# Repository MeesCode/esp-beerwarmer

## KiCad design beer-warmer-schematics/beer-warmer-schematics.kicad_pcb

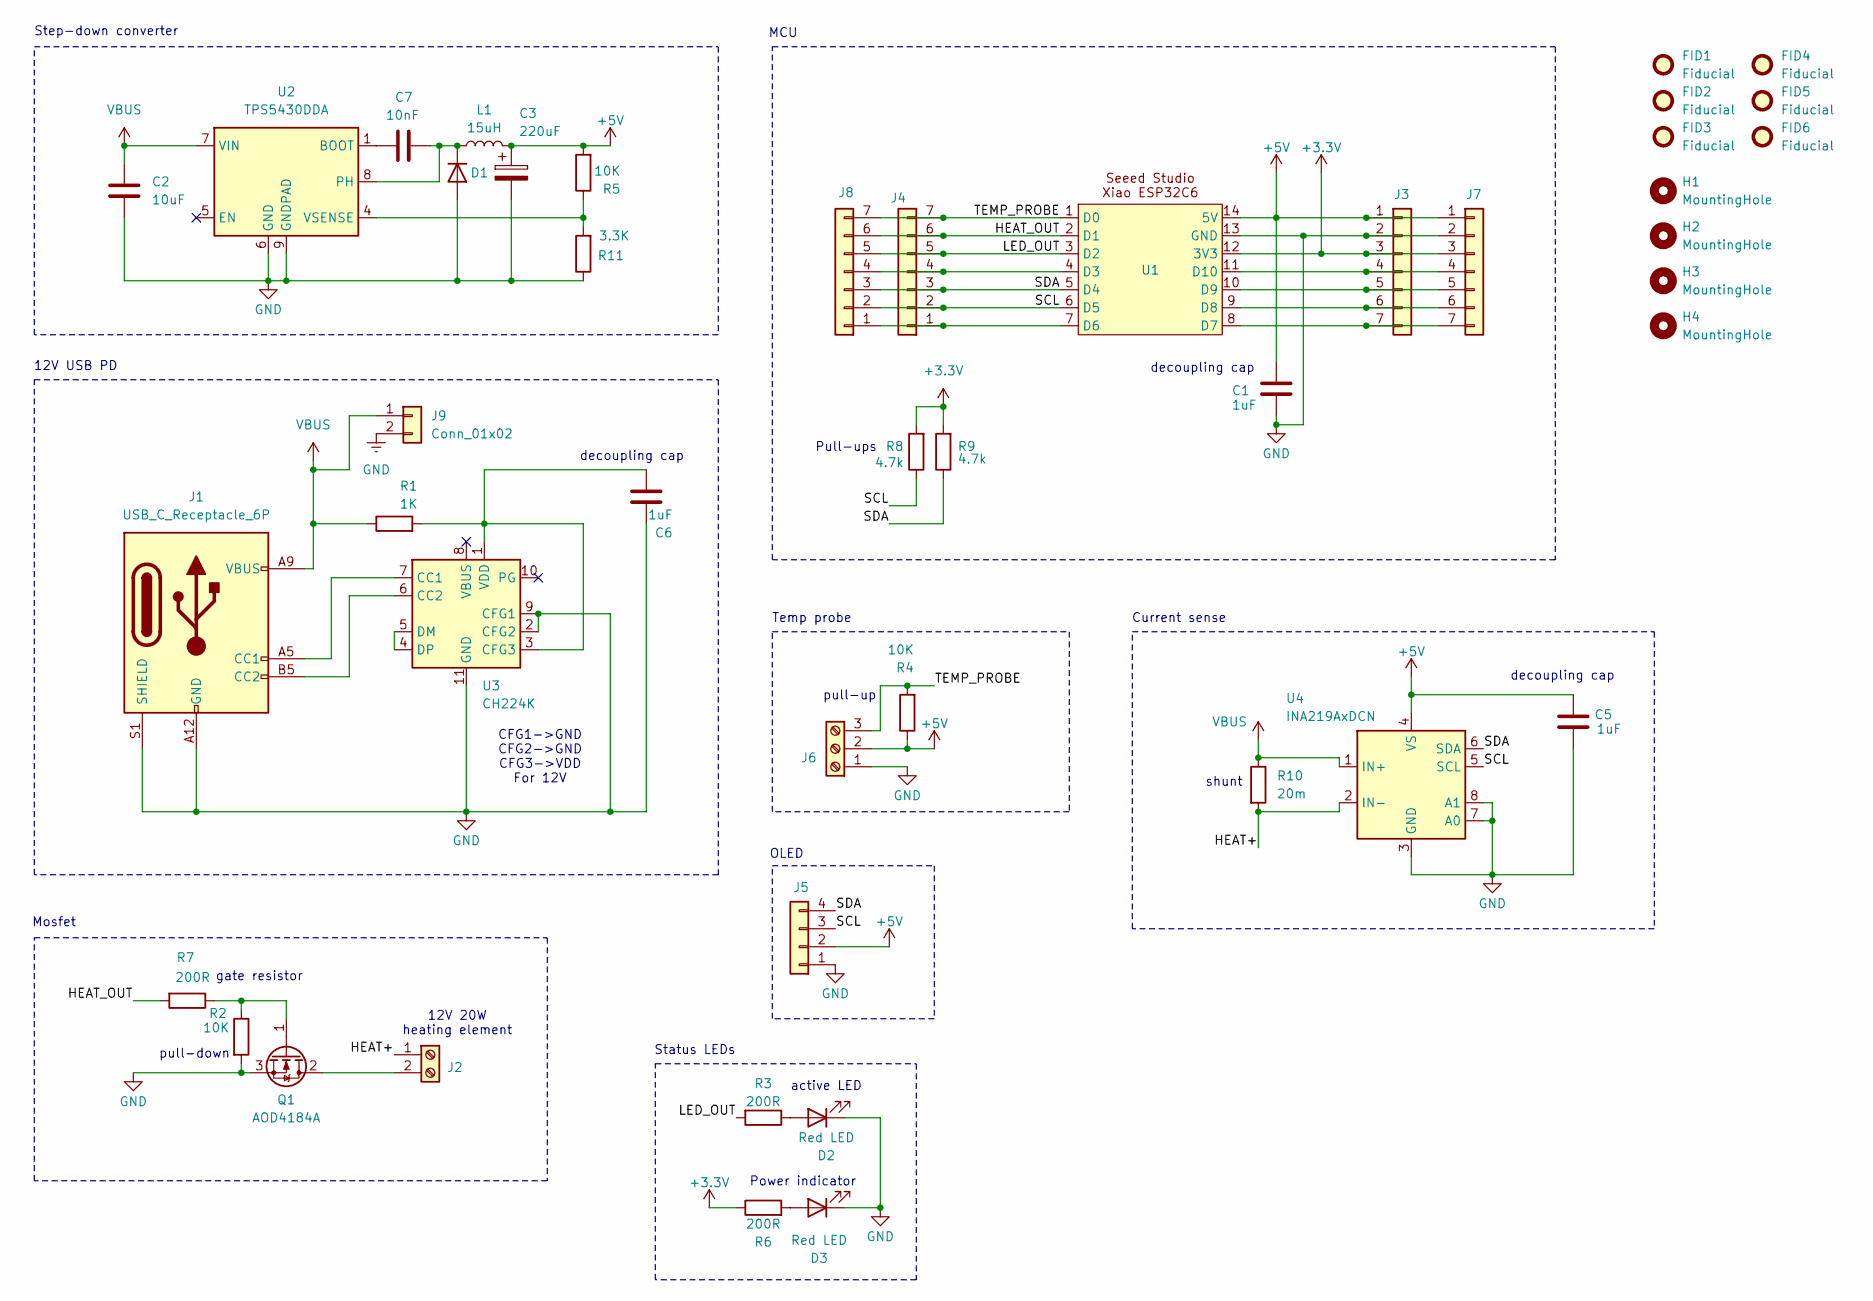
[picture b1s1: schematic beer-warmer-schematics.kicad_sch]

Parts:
C1, C5, C6: 1uF; C_0402_1005Metric; LCSC C52923
C2: 10uF; C_0805_2012Metric; LCSC C15850
C3: 220uF; CP_Elec_6.3x7.7; LCSC C3342
C7: 10nF; C_0402_1005Metric; LCSC C1524
D1: D; D_SMA; Manufacturer # B530C-13-F; LCSC C64982
D2, D3: Red LED; LED_0603_1608Metric; LCSC C2286
FID1, FID2, FID3, FID4, FID5, FID6: Fiducial; Fiducial_0.5mm_Mask1.5mm
H1, H2, H3, H4: MountingHole; MountingHole_3.2mm_M3_DIN965_Pad
J1: USB_C_Receptacle_6P; USB_C_Receptacle_GCT_USB4125-xx-x_6P_TopMnt_Horizontal; Manufacturer # 1054500101; LCSC C456012
J2: Screw_Terminal_01x02; TerminalBlock_Phoenix_MKDS-1,5-2-5.08_1x02_P5.08mm_Horizont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; LCSC C8465
J3, J4: Conn_01x07_Socket; PinSocket_1x07_P2.54mm_Vertical; LCSC C2932672
J5: Conn_01x04_Pin; JST_XH_B4B-XH-A_1x04_P2.50mm_Vertical; LCSC C594232
J6: Screw_Terminal_01x03; TerminalBlock_Phoenix_MKDS-1,5-3-5.08_1x03_P5.08mm_Horizont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; LCSC C72334
J7, J8: Conn_01x07_Socket; PinHeader_1x07_P2.54mm_Vertical; LCSC C2932672
J9: Conn_01x02; PinHeader_1x02_P2.54mm_Vertical
L1: 15uH; L_Changjiang_FNR5040S; LCSC C167969
Q1: AOD4184A; TO-252-2; LCSC C99124
R1: 1K; R_0603_1608Metric; LCSC C21190
R2, R4, R5: 10K; R_0603_1608Metric; LCSC C15401
R3, R6, R7: 200R; R_0603_1608Metric; LCSC C22962
R8, R9: 4.7k; R_0603_1608Metric; LCSC C23162
R10: 20m; R_1206_3216Metric; LCSC C393094
R11: 3.3K; R_0603_1608Metric; LCSC C22978
U1: XIAO-ESP32C6-DIP
U2: TPS5430DDA; TI_SO-PowerPAD-8_ThermalVias; LCSC C9864
U3: CH224K; SSOP-10-1EP_3.9x4.9mm_P1mm_EP2.1x3.3mm; LCSC C970725
U4: INA219AxDCN; SOT-23-8; LCSC C87469

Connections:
+3.3V: J3.3, J7.3, R6.1, R8.2, R9.2, U1.12 (3V3)
+5V: C1.1, C3.1, C5.2, J3.1, J5.2, J6.2, J7.1, L1.2, R4.1, R5.2, U1.14 (5V), U4.4 (VS); also elsewhere on the board
/<NO NET>: J4.4, J8.4, U1.4 (D3)
/HEAT+: J2.1, R10.2, U4.2 (IN-)
/HEAT_OUT: J4.6, J8.6, R7.2, U1.2 (D1)
/LED_OUT: J4.5, J8.5, R3.2, U1.3 (D2)
/SCL: J4.2, J5.3, J8.2, R8.1, U1.6 (D5), U4.5 (SCL)
/SDA: J4.3, J5.4, J8.3, R9.1, U1.5 (D4), U4.6 (SDA)
/TEMP_PROBE: J4.7, J6.3, J8.7, R4.2, U1.1 (D0)
GND: C1.2, C2.2, C3.2, C5.1, C6.1, D1.2 (A), D2.1 (K), D3.1 (K), J1.A12 (GND), J1.B12 (GND), J1.S1 (SHIELD), J3.2, J5.1, J6.1, J7.2, J9.2, Q1.3 (S), R2.2, R11.1, U1.13 (GND), U2.6 (GND), U2.9 (GNDPAD), U3.2 (CFG2), U3.9 (CFG1), U3.11 (GND), U4.3 (GND), U4.7 (A0), U4.8 (A1)
unnamed: C7.1, D1.1 (K), L1.1, U2.8 (PH)
unnamed: D2.2 (A), R3.1
unnamed: D3.2 (A), R6.2
unnamed: J1.A5 (CC1), U3.7 (CC1)
unnamed: J1.B5 (CC2), U3.6 (CC2)
unnamed: J2.2, Q1.2 (D)
unnamed: J3.4, J7.4, U1.11 (D10)
unnamed: J3.5, J7.5, U1.10 (D9)
unnamed: J3.6, J7.6, U1.9 (D8)
unnamed: J3.7, J7.7, U1.8 (D7)
unnamed: J4.1, J8.1, U1.7 (D6)
unnamed: Q1.1 (G), R2.1, R7.1
unnamed: C7.2, U2.1 (BOOT)
unnamed: R5.1, R11.2, U2.4 (VSENSE)
unnamed: C6.2, R1.2, U3.1 (VDD), U3.3 (CFG3)
unnamed: U3.4 (DP), U3.5 (DM)
VBUS: C2.1, J1.A9 (VBUS), J1.B9 (VBUS), J9.1, R1.1, R10.1, U2.7 (VIN), U4.1 (IN+)

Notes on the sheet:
decoupling cap
12V 20W heating element
12V USB PD
Status LEDs
Current sense
OLED
pull-up
Power indicator
gate resistor
shunt
active LED
Step-down converter
Mosfet
Pull-ups
pull-down
CFG1->GND CFG2->GND CFG3->VDD For 12V
MCU
Temp probe

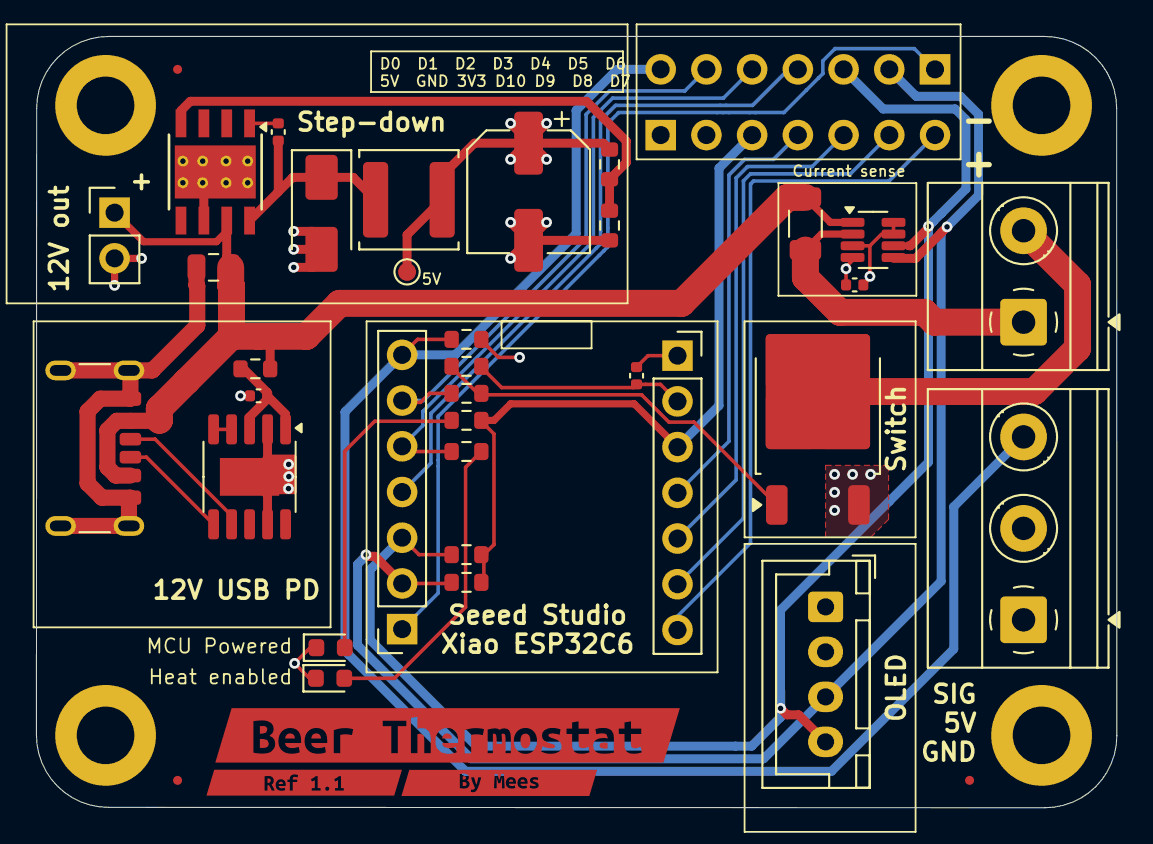
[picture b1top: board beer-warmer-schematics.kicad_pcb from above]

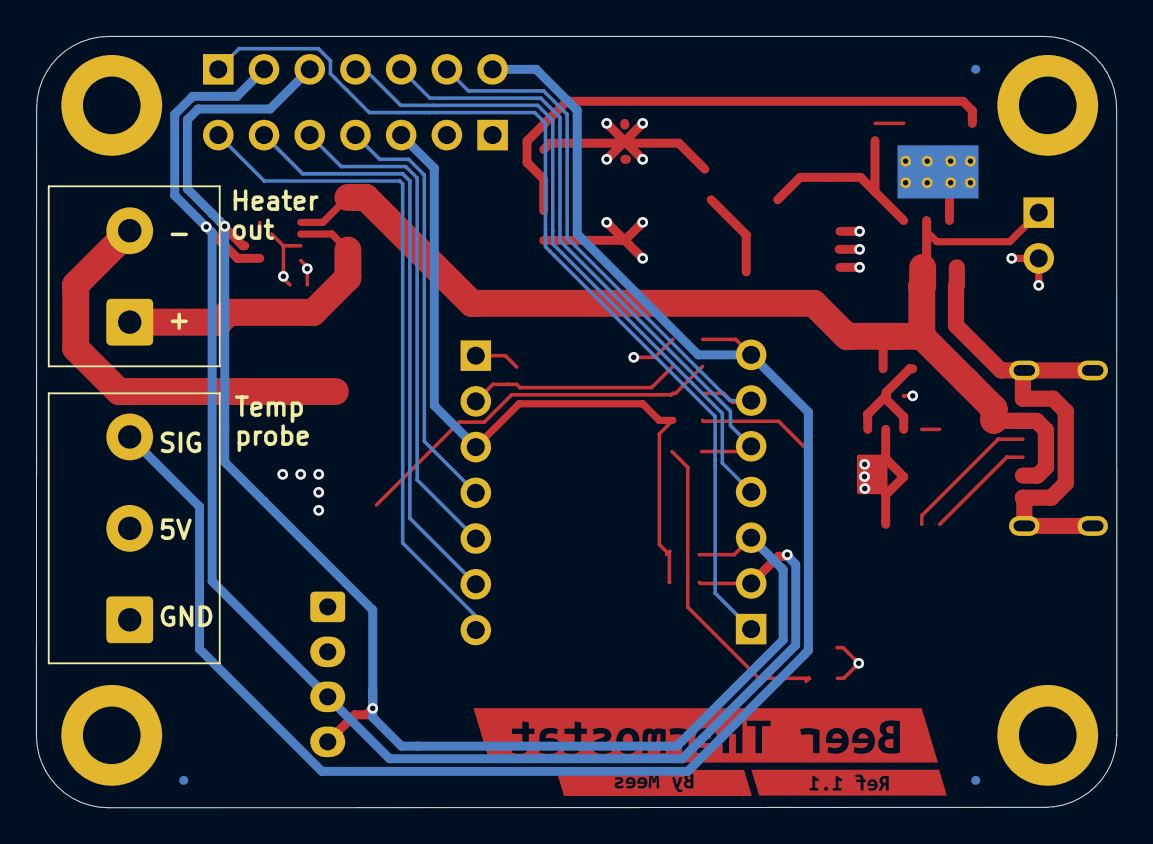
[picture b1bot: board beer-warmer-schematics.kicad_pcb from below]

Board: 4 copper layers, 60.0 x 42.8 mm, 48 parts (3 on the bottom side), 27 nets.

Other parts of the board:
TP2: TestPoint; TestPoint_Pad_D1.0mm
kibuzzard-67EFB7C2: G***; kibuzzard-67EFB7C2
kibuzzard-67EFB7D4: G***; kibuzzard-67EFB7D4
kibuzzard-693FEE7D: G***; kibuzzard-693FEE7D

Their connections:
+5V: TP2.1; also elsewhere on the board

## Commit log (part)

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2025-03-02 panic on report attribute
2025-03-03 fix antenna
2025-03-03 cleanup and remove build files
2025-03-03 add required files
2025-03-03 cleanup, fix led gpio direction
2025-03-05 temp sensor working
2025-03-05 very basic temperature control
2025-03-05 cleanup and add binary output for heater
2025-03-05 fix some reporting issues
2025-03-05 cleanup
2025-03-05 small optimizations
2025-03-07 set target temp and max temp
2025-03-15 support for ssd1306 oled
2025-03-26 display buffer for more control over graphics
2025-03-26 functional graph
2025-03-30 add schematics
2025-03-30 initial routing
2025-03-30 cleanup add more lcsc numbers
2025-03-30 redid board layout
2025-03-30 styling
2025-03-30 fix screw terminal component
2025-03-31 cleanup, update positioning, mess up routing
2025-03-31 power indicator
2025-03-31 remove lck file
2025-03-31 use more standard components
2025-03-31 move extra tracks to other layer
2025-04-01 imperial footprint sizes
2025-04-01 beefier resistor
2025-04-01 save
2025-04-02 fix a bunch of potential issues, add current sense
2025-04-04 middle ground plane, 12v over dedicated tracks to avoid noise
2025-04-04 use a much simpler usb c component
2025-04-04 wider traces
2025-04-07 clean up schematics, correct mosfet orientation
2025-04-07 led indicator on vbus power
2025-04-07 remove some vias
2025-04-07 slightly better decoupling cap placement
2025-04-08 fix active led, bottom silkscreen
2025-04-08 incorporated some feedback
2025-04-08 low side driver
2025-04-09 different step down
2025-04-09 routing overhaul
2025-04-13 active led in parallel with load
2025-04-13 change diode on buck
2025-11-26 updated with new knowledge gained
2025-11-30 production
2025-12-15 updated with learnings after production
2025-12-15 remove designator on silkscreen
2025-12-15 current sense working, oled disabled
2025-12-17 test current reporting zigbee
2025-12-17 zigbee reporting almost working correctly
2025-12-17 good zigbee readouts
2026-03-29 change temperature
